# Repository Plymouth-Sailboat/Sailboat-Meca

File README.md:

# Sailboat-Meca

This repository lists all the mechanical documents of the sailboat - Electronic Board and 3D Parts. It is used in conjunction with the [Arduino Repository](https://github.com/Plymouth-Sailboat/SailBoatArduinoInterface) and the [Raspberry Pi Repository](https://github.com/Plymouth-Sailboat/SailBoatROS).
This project was done by [Ulysse Vautier](https://ulyssevautier.github.io/) for his PhD in Autonomous Sailboat Navigation System at the University of Plymouth.

**A complete tutorial is available on the** [wiki](https://github.com/Plymouth-Sailboat/Sailboat-Meca/wiki).

The goal of such a project is to make an affordable, accessible and expandable control box to transform a RC sailboat into an autonomous Sailboat easily. The control box costs £86 to make.  
Once connected to the different sensors and actuators of the sailboat, it transforms it into an autonomous sailboat with already implemented navigation algorithms. Please see the [list of control algorithms](https://github.com/Plymouth-Sailboat/SailBoatROS/wiki/Controllers-List) already implemented.

Another option is to use off-the-shelf Shields to act as a connector interface for the Arduino. This is a cheaper alternative to the custom board, but removes the compactness of it. This is explained in the [wiki](https://github.com/Plymouth-Sailboat/Sailboat-Meca/wiki).

**For more information look at the Wikis. The project is separated into 3 categories : [SailboatMeca](https://github.com/Plymouth-Sailboat/Sailboat-Meca), [SailBoatROS](https://github.com/Plymouth-Sailboat/SailBoatROS) and [SailboatArduinoInterface](https://github.com/Plymouth-Sailboat/SailBoatArduinoInterface).**

**[SailboatMeca](https://github.com/Plymouth-Sailboat/Sailboat-Meca) explains the hardware configuration of the boat. The sensors that are used, how to build the control box and how to attach all the components to the control box.**

**[SailBoatROS](https://github.com/Plymouth-Sailboat/SailBoatROS) contains the code on the Raspberry Pi. It explains how to have a full environment ready on the Raspberry Pi 3B and Raspberry Pi 3B+ to have a working boat.**

**[SailBoatArduinoInterface](https://github.com/Plymouth-Sailboat/SailBoatArduinoInterface) explains how to upload the code to the Arduino. It also explains how to change the configuration files or how to add sensors to comply with your hardware configuration.  
Please look at all their wikis and READMEs.**

# Structure of this Repository

You fill find the 3D prints for waterproofing our sensors and the complete KiCad project for our Custom Circuit Board. The KiCad projects come with 3D models of the boards and the Gerber files needed to manufacture them.

# Off-The-Shelf System

This is a new hardware architecture using mostly commercial modules for Arduino and Raspberry Pi, using [SeeedStudio grove shields](http://wiki.seeedstudio.com/Grove_System/). This version is a bit bigger but a cheaper and more easily attainable than manufactured custom boards.  
All the previous components used are still compatible, only connectors need to be changed. Also the battery used are Li-ion battery packs now. Everything is explained in the [wiki](https://github.com/Plymouth-Sailboat/Sailboat-Meca/wiki).

# Custom Circuit Board

Our custom board is composed of two boards, stacking with each others. One stacking with the Arduino Mega and another one stacking with the Raspberry Pi.
These custom boards manages power, connection to sensors and motors and communications between Raspberry Pi, the Arduino and all the peripheral devices.

## Arduino Interface Board

The Arduino Interface Board exports the Arduino's connector to interface them with strong, more robust JST connectors. This board also manages the power to all of the peripheral devices. You can find the complete KiCad Project, Gerber files and 3Ds of the boards at [Arduino Interface Board Folder](/Electronic%20Board/Sailboat%20Kicad/Board1-Arduino).  
This board stacks with the Arduio Mega and the Raspberry Pi Interface Board below.

## Raspberry Pi Interface Board

The Raspberry Pi Board is only a board to level all the components to make the overall structure compact. It connects the power to the Raspberry Pi and interface the Radio Receiver to the Arduino. You can find the complete KiCad Project, Gerber files and 3Ds of the boards at [Raspberry Pi Interface Board Folder](/Electronic%20Board/Sailboat%20Kicad/Board2-RPI).   
This board stacks with the Arduino Interface Board and the Raspberry Pi.

# Bill Of Material

The bill of material is available [here](BOM.xlsx). It details all the mechanical and electrical components with the sensors and motors for our boats. It also gives all the link to suppliers to buy the components we use. We mainly purchase our components from [RS](https://uk.rs-online.com/web/) and we use a third-party manufacturer to make the boards [SeeedStudio](https://www.seeedstudio.com/fusion_pcb.html).

The overall price of a whole autonomous sailboat comes to £605.65 (considering the IMU used is 1/3 of the price). The custom board itself costs £86 overall - with third-party service to print the boards.

# Installation

## Requirements

* Raspberry Pi 3 Model B with [ROS and our package](https://github.com/Plymouth-Sailboat/SailBoatROS)
* Arduino Mega with [our code](https://github.com/Plymouth-Sailboat/SailBoatArduinoInterface)
* Custom Boards above

All the installation for each of these devices are explained in their respective Repository.

To get your custom board printed via SeeedStudio, we suggest following the tutorial in the [wiki](https://github.com/Plymouth-Sailboat/Sailboat-Meca/wiki)

Once the boards are soldered all you need is to stack them with the Arduino and Raspberry Pi. Connect your Raspberry Pi to the Arduino via USB and your Control Box is ready to host a new sailboat.

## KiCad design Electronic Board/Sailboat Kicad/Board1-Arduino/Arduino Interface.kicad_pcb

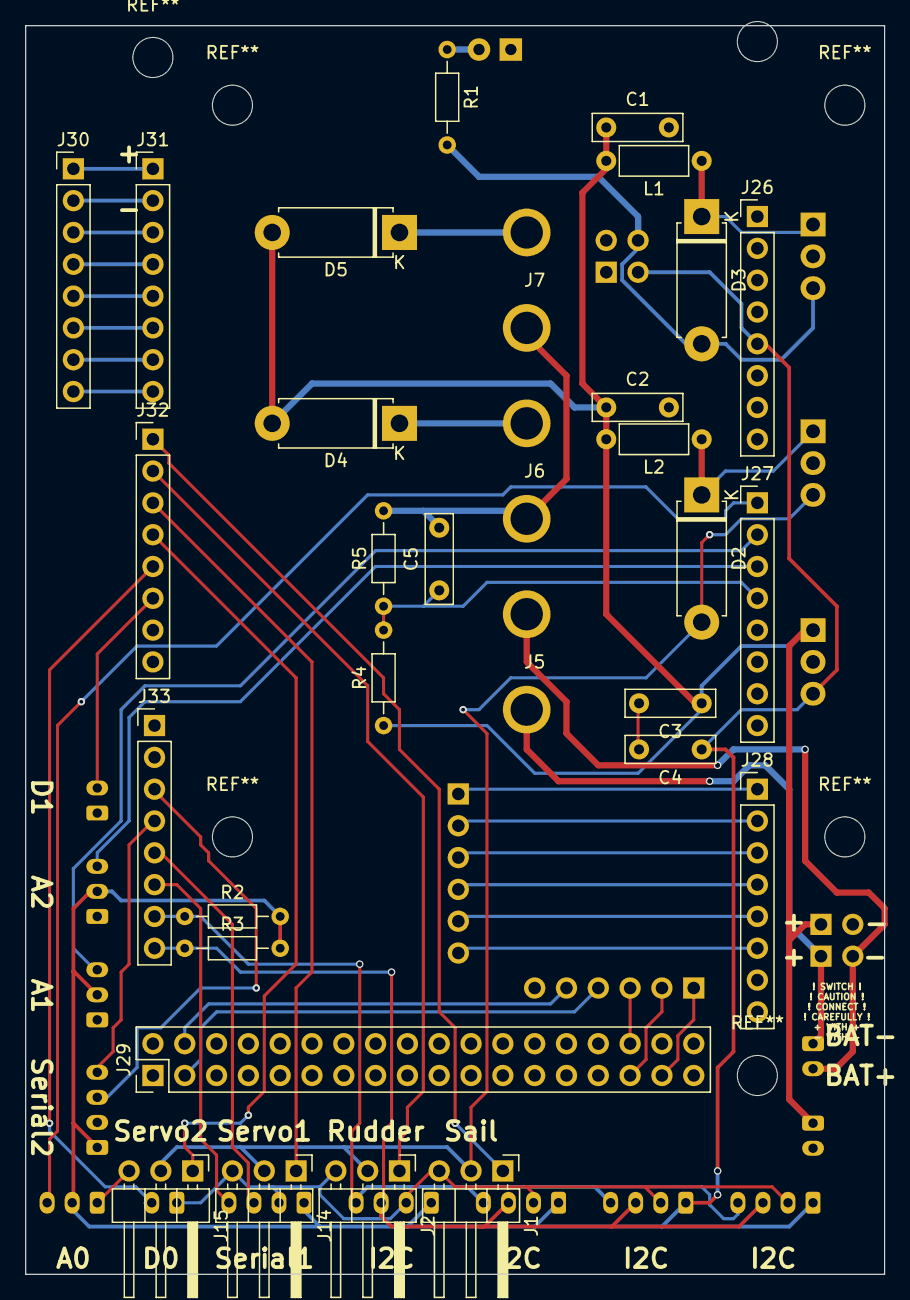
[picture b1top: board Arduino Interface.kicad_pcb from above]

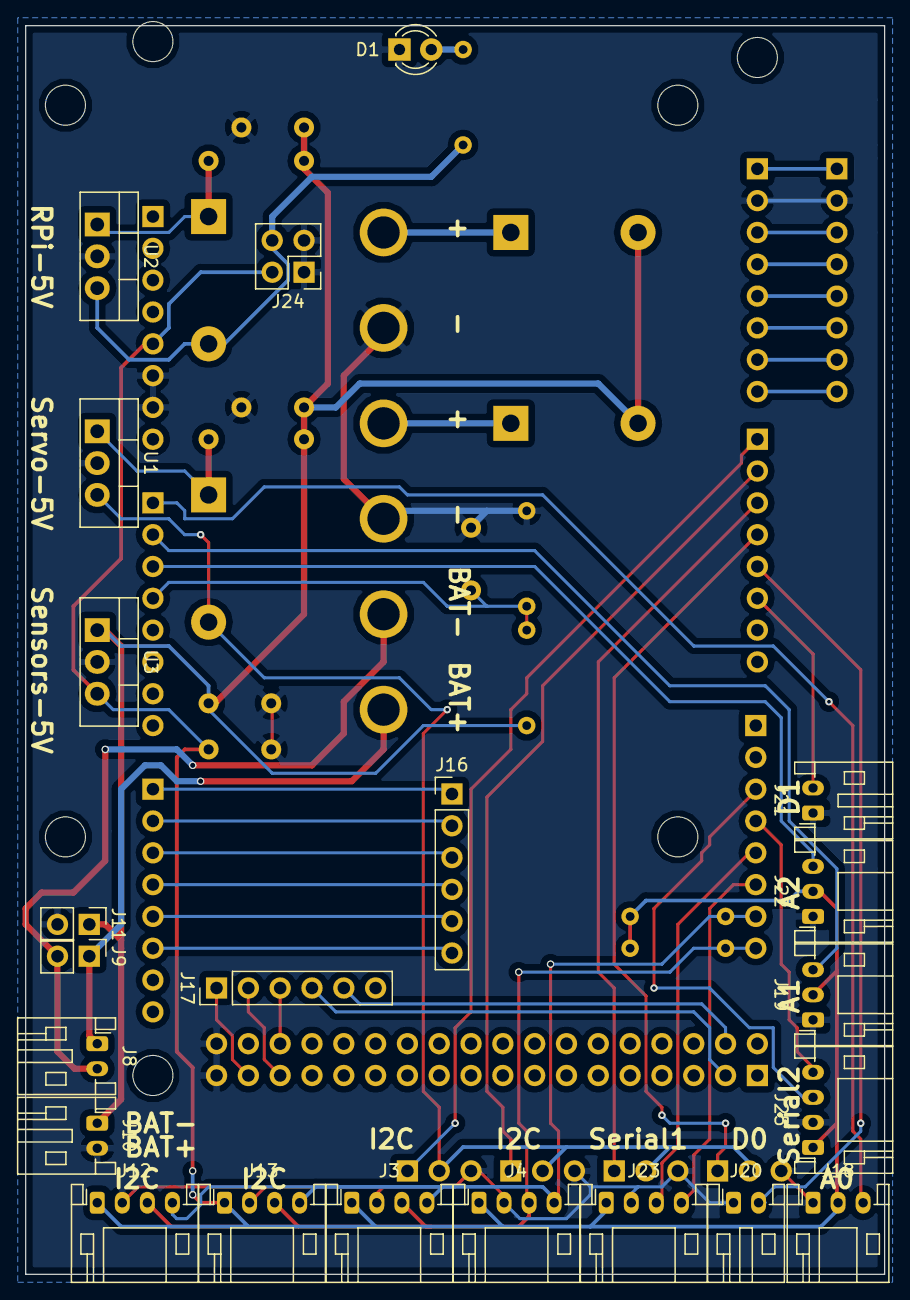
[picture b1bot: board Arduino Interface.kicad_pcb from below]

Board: 2 copper layers, 68.6 x 99.7 mm, 53 parts (22 on the bottom side), 46 nets.

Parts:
C1, C2: 4.7uF; C_Rect_L7.0mm_W2.0mm_P5.00mm
C3: 0.33uF; C_Rect_L7.0mm_W2.0mm_P5.00mm
C4: 0.1uF; C_Rect_L7.0mm_W2.0mm_P5.00mm
C5: 1uF; C_Rect_L7.0mm_W2.0mm_P5.00mm
D1: G; LED_D3.0mm
D2, D3, D4, D5: D_Schottky; D_5W_P10.16mm_Horizontal
J1, J2, J14, J15: Conn_01x03_Male; PinHeader_1x03_P2.54mm_Horizontal
J3, J4, J12, J13, J23, J25: Conn_01x04_Male; JST_PH_S4B-PH-K_1x04_P2.00mm_Horizontal
J5, J6, J7: Conn_01x02_Female; BAT-CONN
J8, J10, J20, J21: Conn_01x02_Male; JST_PH_S2B-PH-K_1x02_P2.00mm_Horizontal
J9, J11: Conn_01x02_Male; PinHeader_1x02_P2.54mm_Vertical
J16, J17: Conn_01x06_Male; PinHeader_1x06_P2.54mm_Vertical
J18, J19, J22: Conn_01x03_Male; JST_PH_S3B-PH-K_1x03_P2.00mm_Horizontal
J24: Conn_02x02_Odd_Even; PinHeader_2x02_P2.54mm_Vertical
J26, J27, J28, J30, J31, J32, J33: Conn_01x08_Male; PinHeader_1x08_P2.54mm_Vertical
J29: Conn_02x18_Odd_Even; PinHeader_2x18_P2.54mm_Vertical
L1, L2: 3.3uH; L_Axial_L5.3mm_D2.2mm_P7.62mm_Horizontal_Vishay_IM-1
R1: 330; R_Axial_DIN0204_L3.6mm_D1.6mm_P7.62mm_Horizontal
R2, R3: 4k7; R_Axial_DIN0204_L3.6mm_D1.6mm_P7.62mm_Horizontal
R4: 20k; R_Axial_DIN0204_L3.6mm_D1.6mm_P7.62mm_Horizontal
R5: 12k; R_Axial_DIN0204_L3.6mm_D1.6mm_P7.62mm_Horizontal
U1, U2, U3: L7805; TO-220-3_Vertical

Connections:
/ArduinoMega/5V: C4.1, J3.1, J4.1, J12.1, J13.1, J18.2, J19.2, J22.2, J23.1, J24.2, J25.1, J26.5, R2.2, R3.2, U3.3
/ArduinoMega/8: J30.8, J31.8
/ArduinoMega/9: J30.7, J31.7
/ArduinoMega/10: J30.6, J31.6
/ArduinoMega/11: J30.5, J31.5
/ArduinoMega/12: J30.4, J31.4
/ArduinoMega/13: J30.3, J31.3
/ArduinoMega/A3: C5.1, J27.4, R4.2, R5.1
/ArduinoMega/AREF: J30.1, J31.1
/Connectors/5V-Rpi: D3.2, J24.4, R1.2, U2.3
/Connectors/5V-Servo: D2.2, J1.2, J2.2, J14.2, J15.2, U1.3
A0: J18.3, J27.1
A1: J19.3, J27.2
A2: J22.3, J27.3
BAT+: C1.1, C2.1, C3.1, D4.2, D5.2, J10.1, J11.1, L1.2, L2.2, R4.1, U3.1
CD: J17.4, J29.3
CS: J17.5, J29.4
D0: J20.2, J32.5
D1: J21.2, J32.6
GND: C1.2, C2.2, C3.2, C4.2, C5.2, D1.1, J1.3, J2.3, J3.2, J4.2, J6.1, J7.1, J10.2, J11.2, J12.2, J13.2, J14.3, J15.3, J18.1, J19.1, J20.1, J21.1, J22.1, J23.2, J24.1, J24.3, J25.2, J26.6, J26.7, J29.35, J29.36, J30.2, J31.2, R5.2, U1.2, U2.2, U3.2
MISO: J17.2, J29.31
MOSI: J17.3, J29.32
unnamed: D1.2, R1.1
unnamed: D2.1, L2.1, U1.1
unnamed: D3.1, L1.1, U2.1
unnamed: D4.1, J6.2
unnamed: D5.1, J7.2
unnamed: J5.1, J8.1, J9.1
unnamed: J5.2, J8.2, J9.2
RC1: J16.1, J28.1
RC2: J16.2, J28.2
RC3: J16.3, J28.3
RC4: J16.4, J28.4
RC5: J16.5, J28.5
RC6: J16.6, J28.6
RX_1: J23.4, J33.6
RX_2: J25.4, J33.4
Rudder: J2.1, J32.2
SCK: J17.1, J29.33
SCL: J3.3, J4.3, J12.3, J13.3, J33.8, R3.1
SDA: J3.4, J4.4, J12.4, J13.4, J33.7, R2.1
Sail: J1.1, J32.1
Servo1: J14.1, J32.3
Servo2: J15.1, J32.4
TX_1: J23.3, J33.5
TX_2: J25.3, J33.3

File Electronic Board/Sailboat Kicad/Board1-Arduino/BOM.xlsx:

Id | Designator | Package | Quantity | Designation | Supplier and ref
1 | J20,J8,J10,J21 | JST_PH_S2B-PH-K_1x02_P2.00mm_Horizontal | 4 | Conn_01x02_Male
2 | D1 | LED_D3.0mm | 1 | G
3 | REF**,REF**,REF**,REF**,REF**,REF**,REF** | MountingHole_3.2mm_M3 | 7 | MountingHole_3.2mm_M3
4 | J28,J30,J32,J27,J31,J33,J26 | PinHeader_1x08_P2.54mm_Vertical | 7 | Conn_01x08_Male
5 | J29 | PinHeader_2x18_P2.54mm_Vertical | 1 | Conn_02x18_Odd_Even
6 | J4,J3,J13,J23,J25,J12 | JST_PH_S4B-PH-K_1x04_P2.00mm_Horizontal | 6 | Conn_01x04_Male
7 | J5,J7,J6 | BAT-CONN | 3 | Conn_01x02_Female
8 | J18,J19,J22 | JST_PH_S3B-PH-K_1x03_P2.00mm_Horizontal | 3 | Conn_01x03_Male
9 | J1,J15,J14,J2 | PinHeader_1x03_P2.54mm_Horizontal | 4 | Conn_01x03_Male
10 | J11,J9 | PinHeader_1x02_P2.54mm_Vertical | 2 | Conn_01x02_Male
11 | J24 | PinHeader_2x02_P2.54mm_Vertical | 1 | Conn_02x02_Odd_Even
12 | J16,J17 | PinHeader_1x06_P2.54mm_Vertical | 2 | Conn_01x06_Male
13 | R5 | R_Axial_DIN0204_L3.6mm_D1.6mm_P7.62mm_Horizontal | 1 | 12k
14 | R2,R3 | R_Axial_DIN0204_L3.6mm_D1.6mm_P7.62mm_Horizontal | 2 | 4k7
15 | R4 | R_Axial_DIN0204_L3.6mm_D1.6mm_P7.62mm_Horizontal | 1 | 20k
16 | U3,U1,U2 | TO-220-3_Vertical | 3 | L7805
17 | L1,L2 | L_Axial_L5.3mm_D2.2mm_P7.62mm_Horizontal_Vishay_IM-1 | 2 | 3.3uH
18 | C1,C2 | C_Rect_L7.0mm_W2.0mm_P5.00mm | 2 | 4.7uF
19 | R1 | R_Axial_DIN0204_L3.6mm_D1.6mm_P7.62mm_Horizontal | 1 | 330
20 | D4,D5,D2,D3 | D_5W_P10.16mm_Horizontal | 4 | D_Schottky
21 | C3 | C_Rect_L7.0mm_W2.0mm_P5.00mm | 1 | 0.33uF
22 | C4 | C_Rect_L7.0mm_W2.0mm_P5.00mm | 1 | 0.1uF
23 | C5 | C_Rect_L7.0mm_W2.0mm_P5.00mm | 1 | 1uF

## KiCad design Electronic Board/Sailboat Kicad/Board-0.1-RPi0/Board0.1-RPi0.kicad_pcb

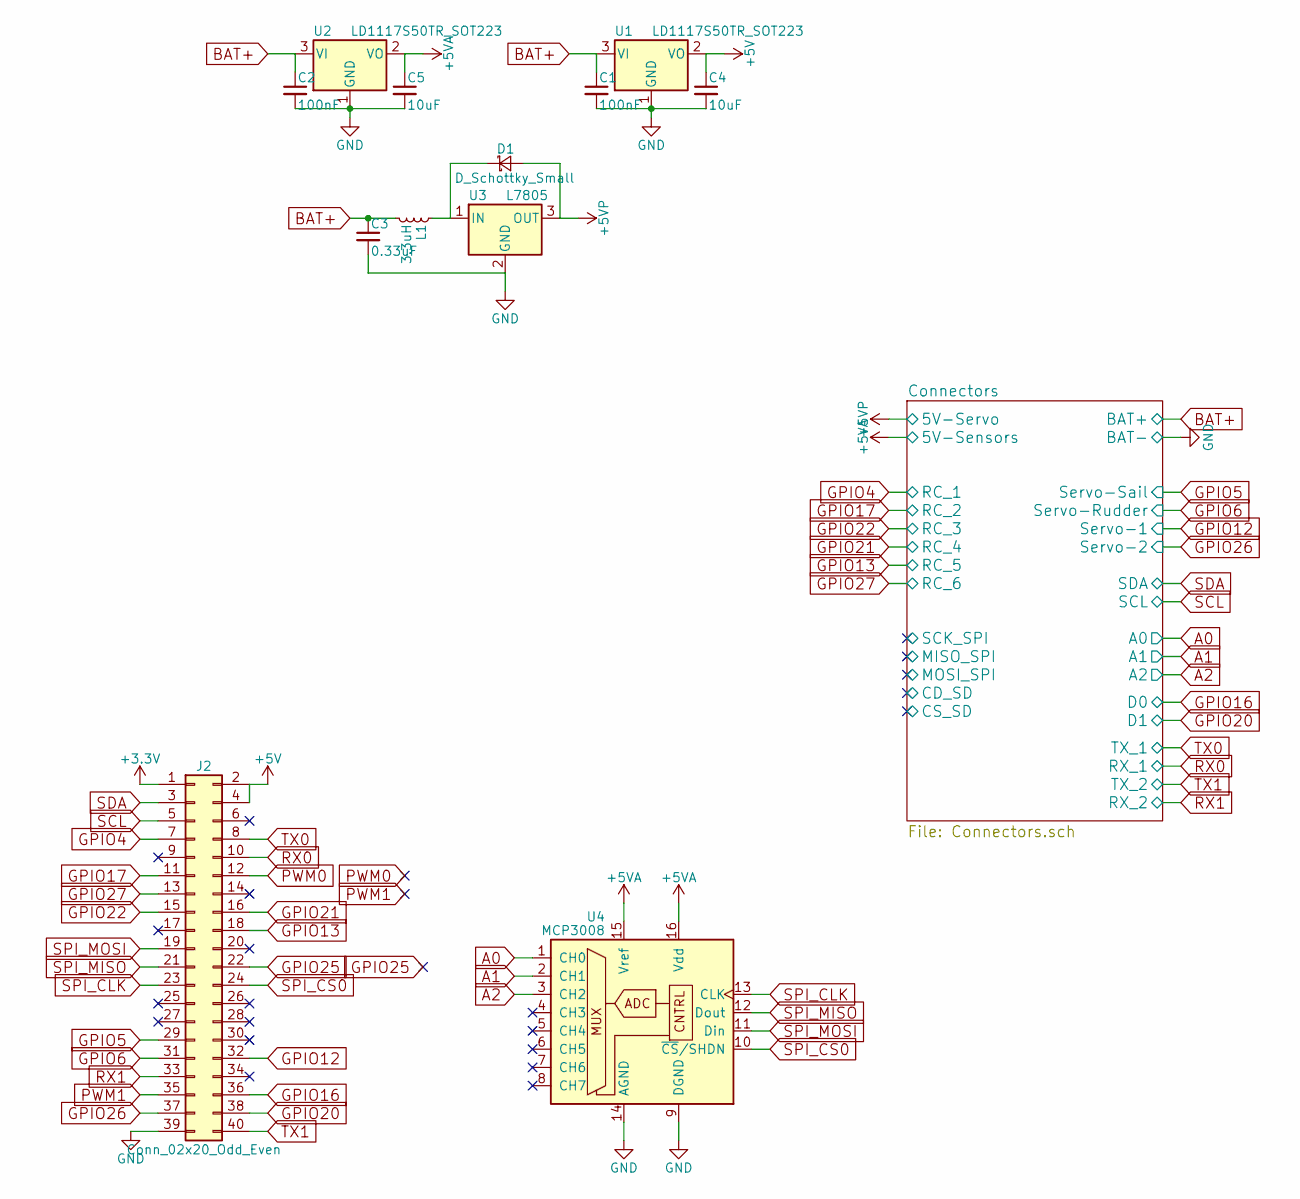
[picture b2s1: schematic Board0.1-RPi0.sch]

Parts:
C1, C2: 100nF; C_0603
C3: 0.33uF; C_0603
C4, C5: 10uF; C_0603
D1: D_Schottky_Small; D_1206
J2: Conn_02x20_Odd_Even; Pin_Header_Straight_2x20_Pitch2.54mm
L1: 3.3uH; L_0603
U1, U2: LD1117S50TR_SOT223; SOT-223-3_TabPin2
U3: L7805; TO-220-3_Vertical
U4: MCP3008; SOIC-16_3.9x9.9mm_Pitch1.27mm

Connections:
+3V3: J2.1
+5V: C4.1, J2.2, J2.4, U1.2 (VO)
+5VA: C5.1, U2.2 (VO), U4.15 (Vref), U4.16 (Vdd); also elsewhere on the board
+5VP: D1.2 (A), U3.3 (OUT); also elsewhere on the board
A0: U4.1 (CH0); also elsewhere on the board
A1: U4.2 (CH1); also elsewhere on the board
A2: U4.3 (CH2); also elsewhere on the board
BAT+: C1.1, C2.1, C3.1, L1.2, U1.3 (VI), U2.3 (VI); also elsewhere on the board
GND: C1.2, C2.2, C3.2, C4.2, C5.2, J2.39, U1.1 (GND), U2.1 (GND), U3.2 (GND), U4.9 (DGND), U4.14 (AGND); also elsewhere on the board
GPIO4: J2.7; also elsewhere on the board
GPIO5: J2.29; also elsewhere on the board
GPIO6: J2.31; also elsewhere on the board
GPIO12: J2.32; also elsewhere on the board
GPIO13: J2.18; also elsewhere on the board
GPIO16: J2.36; also elsewhere on the board
GPIO17: J2.11; also elsewhere on the board
GPIO20: J2.38; also elsewhere on the board
GPIO21: J2.16; also elsewhere on the board
GPIO22: J2.15; also elsewhere on the board
GPIO25: J2.22
GPIO26: J2.37; also elsewhere on the board
GPIO27: J2.13; also elsewhere on the board
unnamed: D1.1 (K), L1.1, U3.1 (IN)
PWM0: J2.12
PWM1: J2.35
RX0: J2.10; also elsewhere on the board
RX1: J2.33; also elsewhere on the board
SCL: J2.5; also elsewhere on the board
SDA: J2.3; also elsewhere on the board
SPI_CLK: J2.23, U4.13 (CLK)
SPI_CS0: J2.24, U4.10 (~CS~/SHDN)
SPI_MISO: J2.21, U4.12 (Dout)
SPI_MOSI: J2.19, U4.11 (Din)
TX0: J2.8; also elsewhere on the board
TX1: J2.40; also elsewhere on the board

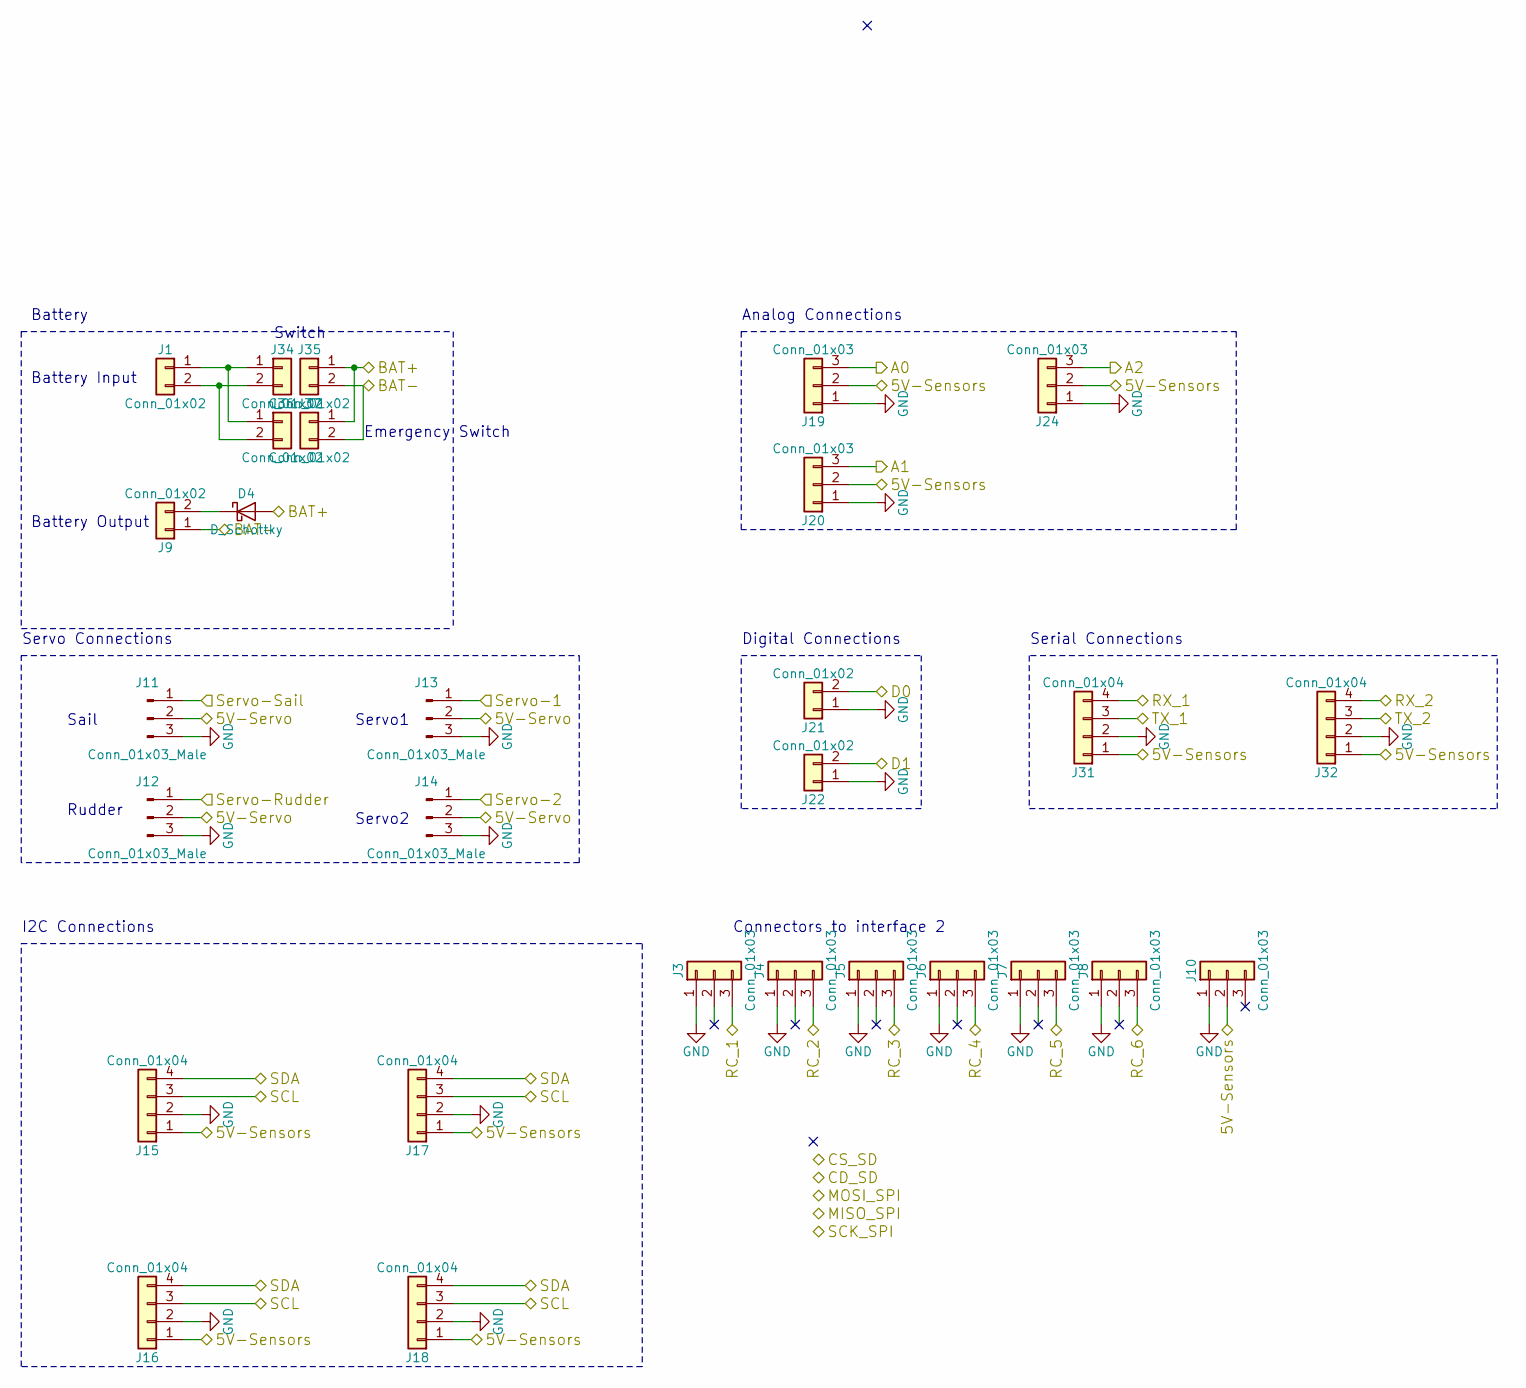
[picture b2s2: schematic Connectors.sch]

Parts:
D4: D_Schottky; D_5W_P10.16mm_Horizontal
J1, J9: Conn_01x02; BAT-CONN
J3, J4, J5, J6, J7, J8, J10: Conn_01x03; Pin_Header_Straight_1x03_Pitch2.54mm
J11, J12, J13, J14: Conn_01x03_Male; Pin_Header_Angled_1x03_Pitch2.54mm
J15, J16, J17, J18, J31, J32: Conn_01x04; JST_PH_S4B-PH-K_04x2.00mm_Angled
J19, J20, J24: Conn_01x03; JST_PH_S3B-PH-K_03x2.00mm_Angled
J21, J22: Conn_01x02; JST_PH_S2B-PH-K_02x2.00mm_Angled
J34, J35, J36, J37: Conn_01x02; Pin_Header_Straight_1x02_Pitch2.54mm

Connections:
+5VA: J10.2, J15.1, J16.1, J17.1, J18.1, J19.2, J20.2, J24.2, J31.1, J32.1; also elsewhere on the board
+5VP: J11.2, J12.2, J13.2, J14.2; also elsewhere on the board
A0: J19.3; also elsewhere on the board
A1: J20.3; also elsewhere on the board
A2: J24.3; also elsewhere on the board
BAT+: D4.2 (A), J35.1, J37.1; also elsewhere on the board
GND: J3.1, J4.1, J5.1, J6.1, J7.1, J8.1, J9.1, J10.1, J11.3, J12.3, J13.3, J14.3, J15.2, J16.2, J17.2, J18.2, J19.1, J20.1, J21.1, J22.1, J24.1, J31.2, J32.2, J35.2, J37.2; also elsewhere on the board
GPIO4: J3.3; also elsewhere on the board
GPIO5: J11.1; also elsewhere on the board
GPIO6: J12.1; also elsewhere on the board
GPIO12: J13.1; also elsewhere on the board
GPIO13: J7.3; also elsewhere on the board
GPIO16: J21.2; also elsewhere on the board
GPIO17: J4.3; also elsewhere on the board
GPIO20: J22.2; also elsewhere on the board
GPIO21: J6.3; also elsewhere on the board
GPIO22: J5.3; also elsewhere on the board
GPIO26: J14.1; also elsewhere on the board
GPIO27: J8.3; also elsewhere on the board
unnamed: D4.1 (K), J9.2
unnamed: J1.1, J34.1, J36.1
unnamed: J1.2, J34.2, J36.2
RX0: J31.4; also elsewhere on the board
RX1: J32.4; also elsewhere on the board
SCL: J15.3, J16.3, J17.3, J18.3; also elsewhere on the board
SDA: J15.4, J16.4, J17.4, J18.4; also elsewhere on the board
TX0: J31.3; also elsewhere on the board
TX1: J32.3; also elsewhere on the board

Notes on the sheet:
Battery Input
Battery Output
Servo Connections
I2C Connections
Sail
Rudder
Servo1
Servo2
Analog Connections
Battery
Digital Connections
Serial Connections
Switch
Emergency Switch
Connectors to interface 2

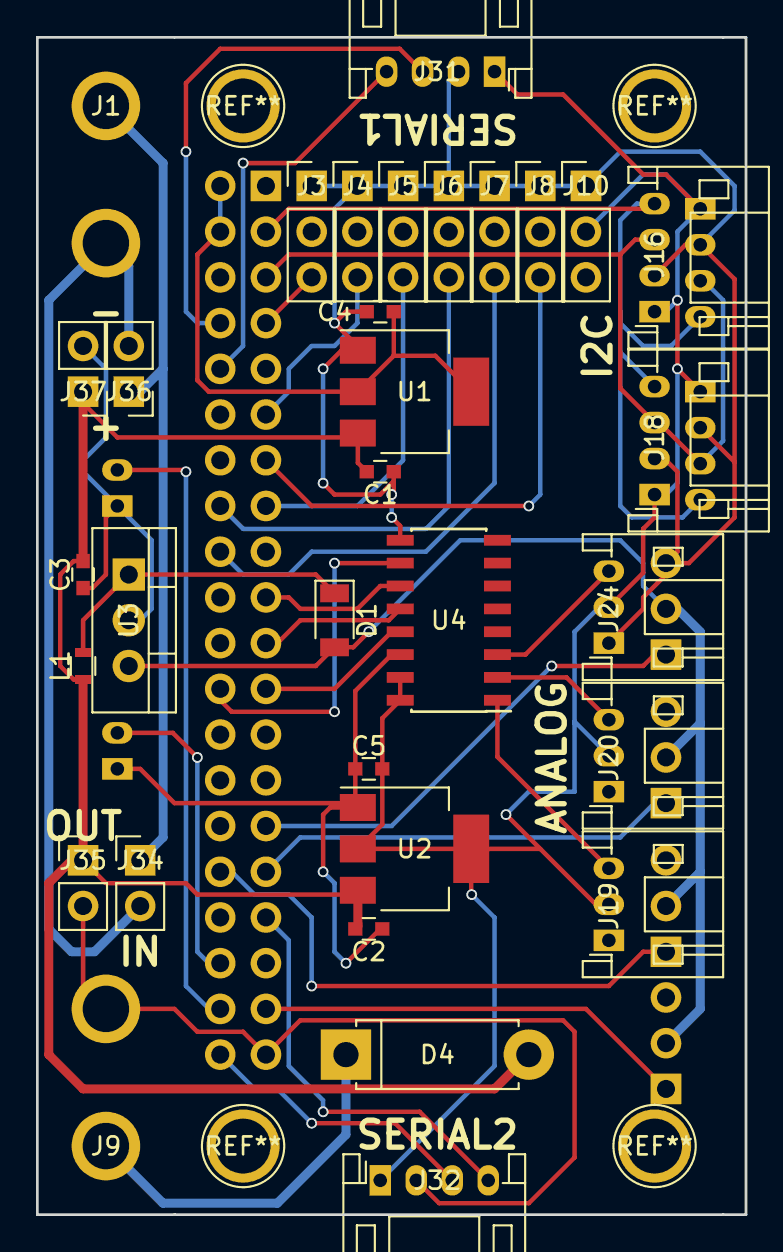
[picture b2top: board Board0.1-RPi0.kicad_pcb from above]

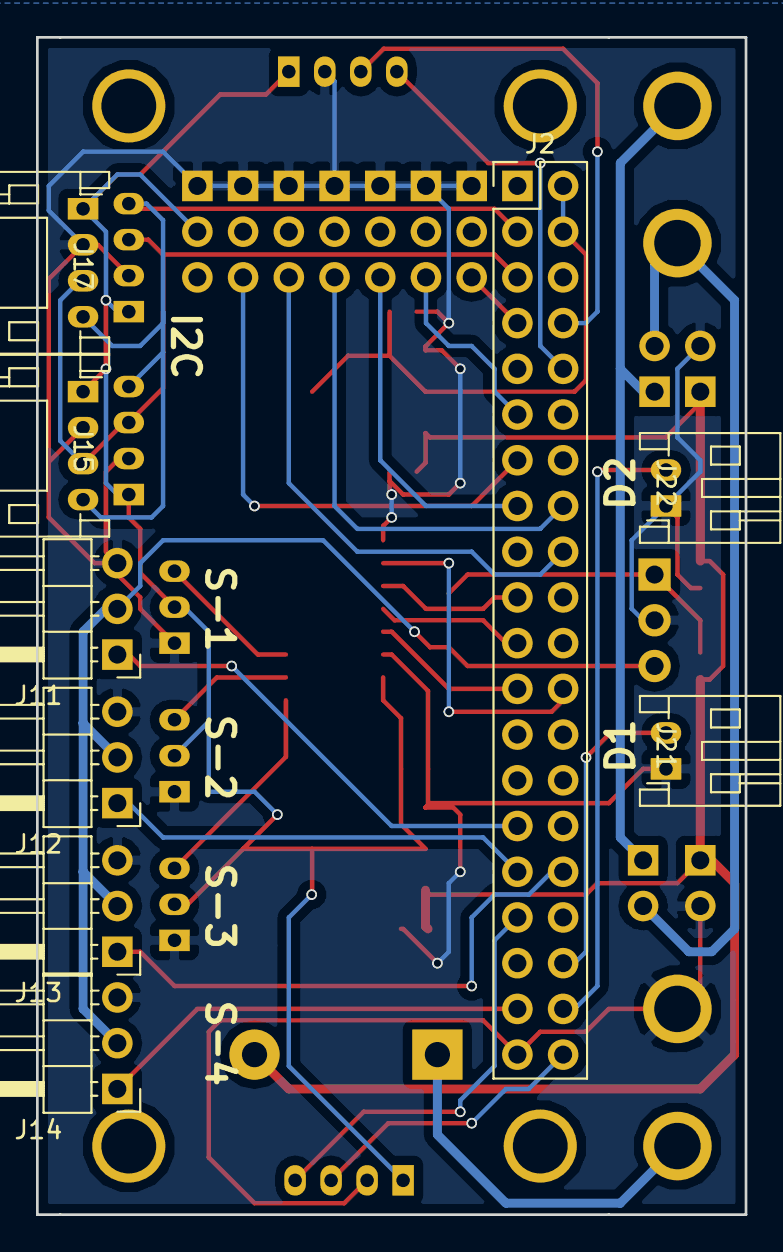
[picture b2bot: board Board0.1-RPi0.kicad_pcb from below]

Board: 2 copper layers, 39.4 x 65.4 mm, 41 parts (9 on the bottom side), 34 nets.

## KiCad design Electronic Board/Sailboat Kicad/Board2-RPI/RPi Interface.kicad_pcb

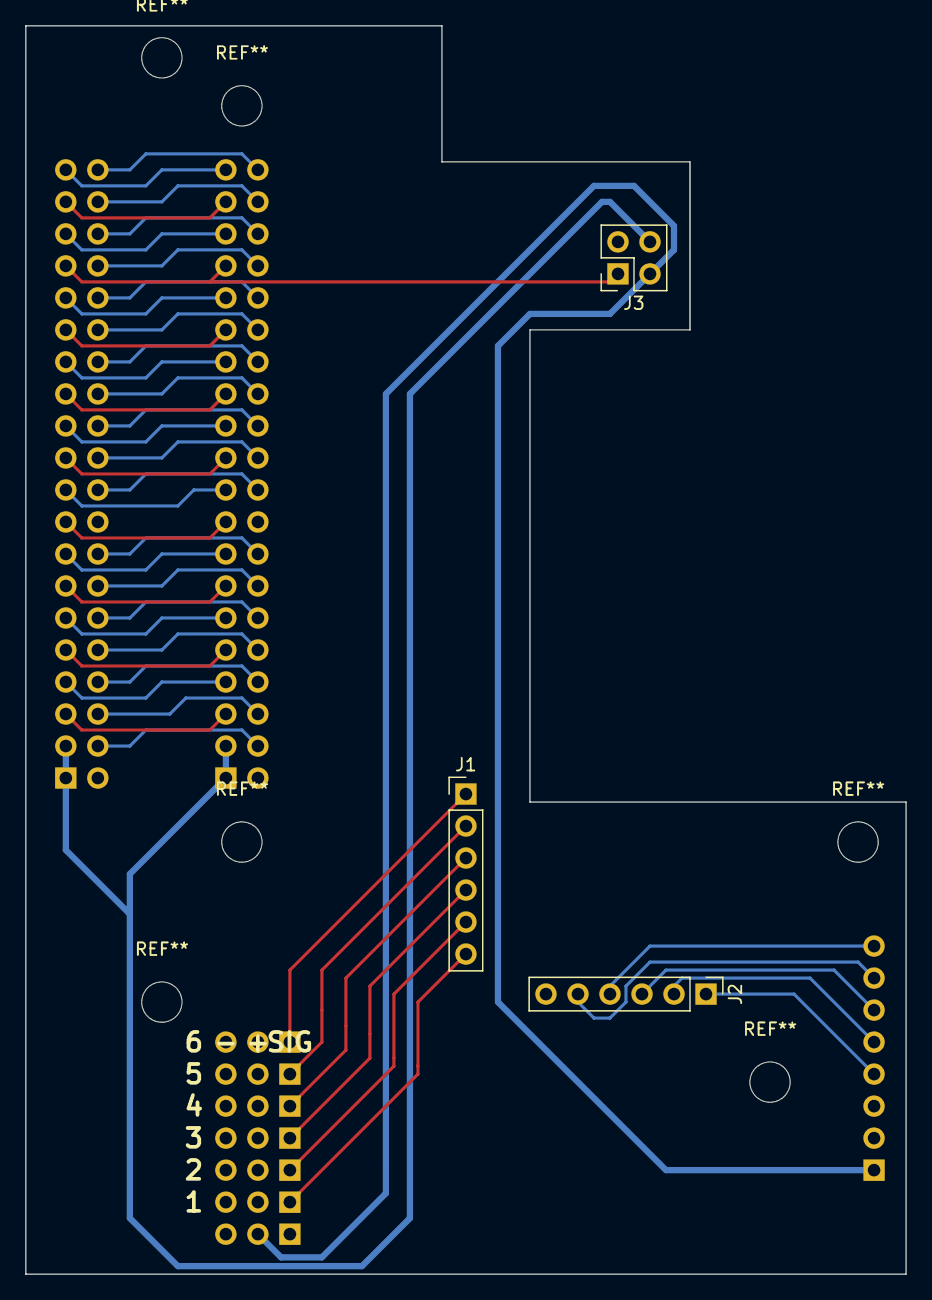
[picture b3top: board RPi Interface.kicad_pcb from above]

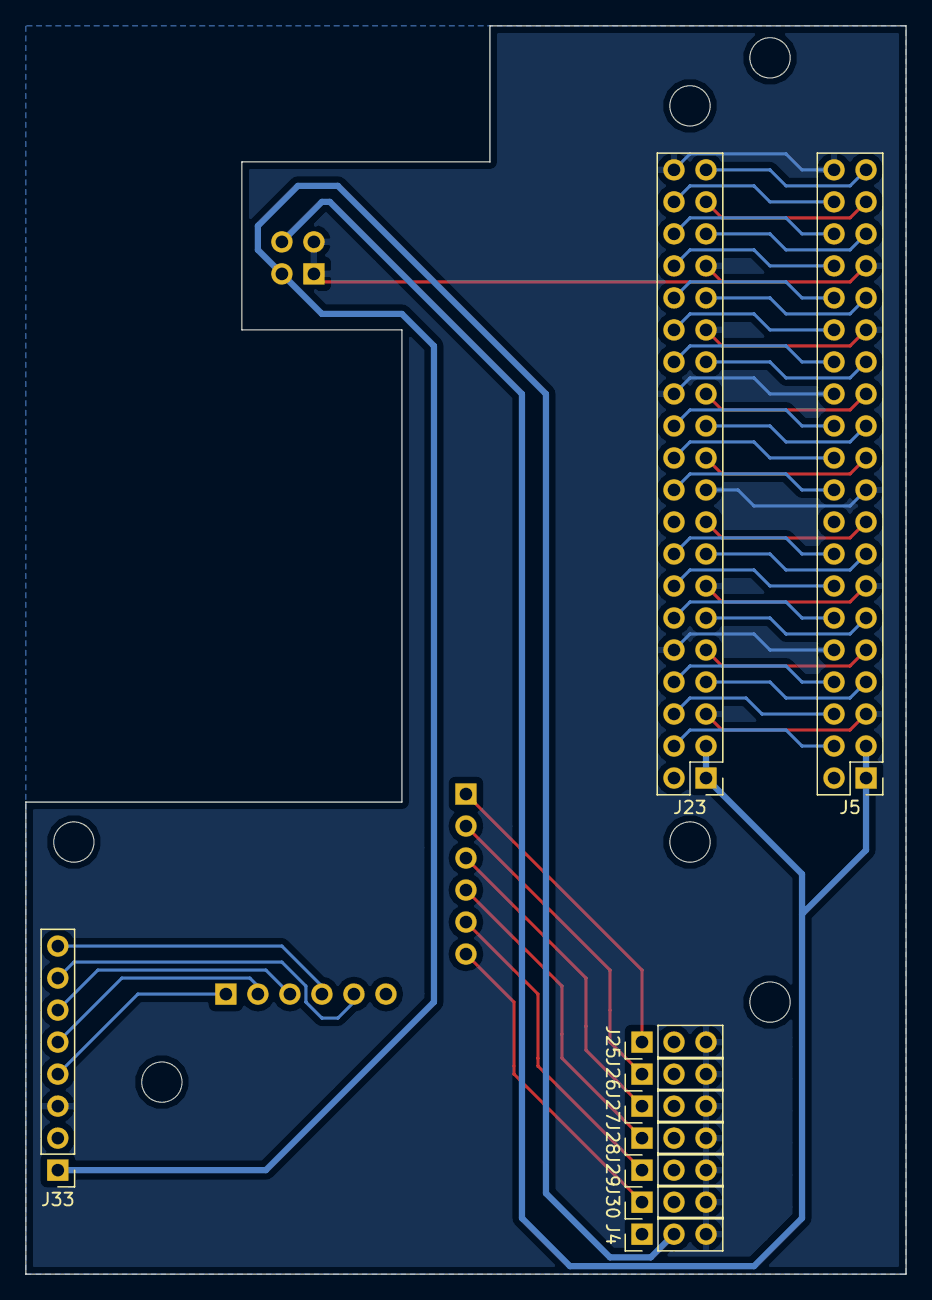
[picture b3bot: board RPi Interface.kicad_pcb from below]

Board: 2 copper layers, 69.9 x 99.1 mm, 13 parts (10 on the bottom side), 42 nets.

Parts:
J1, J2: Conn_01x06; Socket_Strip_Straight_1x06_Pitch2.54mm
J3: Conn_02x02_Odd_Even; Socket_Strip_Straight_2x02_Pitch2.54mm
J4, J25, J26, J27, J28, J29, J30: Conn_01x03_Female; Socket_Strip_Straight_1x03_Pitch2.54mm
J5, J23: Conn_02x20_Odd_Even; Pin_Header_Straight_2x20_Pitch2.54mm
J33: Conn_01x08_Female; Socket_Strip_Straight_1x08_Pitch2.54mm

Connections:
5V-Sensors: J3.2, J4.2, J33.1
/Connectors/5V-RPi: J3.4, J5.1, J5.3, J23.1, J23.3
/RPi/2_RPi: J5.4, J23.4
/RPi/3_RPi: J5.6, J23.6
/RPi/4_RPi: J5.8, J23.8
/RPi/5_RPi: J5.30, J23.30
/RPi/6_RPi: J5.32, J23.32
/RPi/7_RPi: J5.25, J23.25
/RPi/8_RPi: J5.23, J23.23
/RPi/9_RPi: J5.22, J23.22
/RPi/10_RPi: J5.20, J23.20
/RPi/11_RPi: J5.24, J23.24
/RPi/12_RPi: J5.31, J23.31
/RPi/13_RPi: J5.34, J23.34
/RPi/14_RPi: J5.7, J23.7
/RPi/15_RPi: J5.9, J23.9
/RPi/16_RPi: J5.35, J23.35
/RPi/17_RPi: J5.12, J23.12
/RPi/18_RPi: J5.11, J23.11
/RPi/19_RPi: J5.36, J23.36
/RPi/20_RPi: J5.37, J23.37
/RPi/21_RPi: J5.39, J23.39
/RPi/22_RPi: J5.16, J23.16
/RPi/23_RPi: J5.15, J23.15
/RPi/24_RPi: J5.17, J23.17
/RPi/25_RPi: J5.21, J23.21
/RPi/26_RPi: J5.38, J23.38
/RPi/27_RPi: J5.14, J23.14
/RPi/ID_SC: J5.27, J23.27
/RPi/ID_SD: J5.28, J23.28
CD_SD: J2.4, J33.8
CS_SD: J2.5, J33.7
GND: J3.1, J3.3, J4.3, J5.5, J5.10, J5.13, J5.19, J5.26, J5.29, J5.33, J5.40, J23.5, J23.10, J23.13, J23.19, J23.26, J23.29, J23.33, J23.40, J25.3, J26.3, J27.3, J28.3, J29.3, J30.3, J33.3
MISO_SPI: J2.2, J33.5
MOSI_SPI: J2.3, J33.6
RC_1: J1.1, J25.1
RC_2: J1.2, J26.1
RC_3: J1.3, J27.1
RC_4: J1.4, J28.1
RC_5: J1.5, J29.1
RC_6: J1.6, J30.1
SCK_SPI: J2.1, J33.4

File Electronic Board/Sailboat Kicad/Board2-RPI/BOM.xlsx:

Id | Designator | Package | Quantity | Designation | Supplier and ref
1 | J29,J25,J26,J27,J28,J30,J4 | Socket_Strip_Straight_1x03_Pitch2.54mm | 7 | Conn_01x03_Female
2 | J33 | Socket_Strip_Straight_1x08_Pitch2.54mm | 1 | Conn_01x08_Female
3 | J23,J5 | Pin_Header_Straight_2x20_Pitch2.54mm | 2 | Conn_02x20_Odd_Even
4 | J1,J2 | Socket_Strip_Straight_1x06_Pitch2.54mm | 2 | Conn_01x06
5 | J3 | Socket_Strip_Straight_2x02_Pitch2.54mm | 1 | Conn_02x02_Odd_Even
6 | REF**,REF**,REF**,REF**,REF**,REF** | MountingHole_3.2mm_M3 | 6 | MountingHole_3.2mm_M3
